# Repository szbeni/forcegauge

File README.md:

# Force Gauge

- ESP32 based Force Gauge - Aiming to help rock climbing specific training (finger excercises)
- Real time plotting via wifi Webapp/Android app

# Pictures
## Forcegauge with fingerboard

## First prototypes

# Hardware
## Main parts
 - ESP32-C3 MCU
 - 3 buttons
 - OLED screen 0.96" SSD1306
 - Battery with charger
 - USB UART connection
 - HX711 ADC - Load cell
## Schematic ##

- [Schematic](https://github.com/szbeni/forcegauge/blob/main/hw/forcegauge/forcegauge.pdf)
## PCB 

Pictures of the PCB:

## Interactive BOM

- [Interactive BOM](https://htmlpreview.github.io/?https://github.com/szbeni/forcegauge/blob/main/hw/forcegauge/bom/ibom.html)

# Software

## Firmware
- Arudino IDE - Some lagging issues due to limitations of arduino environment
- Started wokring on firmware with ESP-IDF which supports multitasking
- Added Bluetooth support to come up as a Tindeq Progressor bluetooth device (https://tindeq.com/product/progressor) (CChange Bluetooth and restart device, WIFI wont work when BT is on)
- Added Bluetooth support to come up as a Climbro bluetooth device (https://climbro.com/) (Change Bluetooth settings and restart device, WIFI wont work when BT is on)

## Flutter based app (Tested on Android)
- Available on Google play: https://play.google.com/store/apps/details?id=com.github.szbeni.forcegauge
- Real time plotting
- Built in tabata timer (Based on https://github.com/insin/tabata_timer)
- Record history of traning 

## Webapp
- Simple webapp served from a HTTP server

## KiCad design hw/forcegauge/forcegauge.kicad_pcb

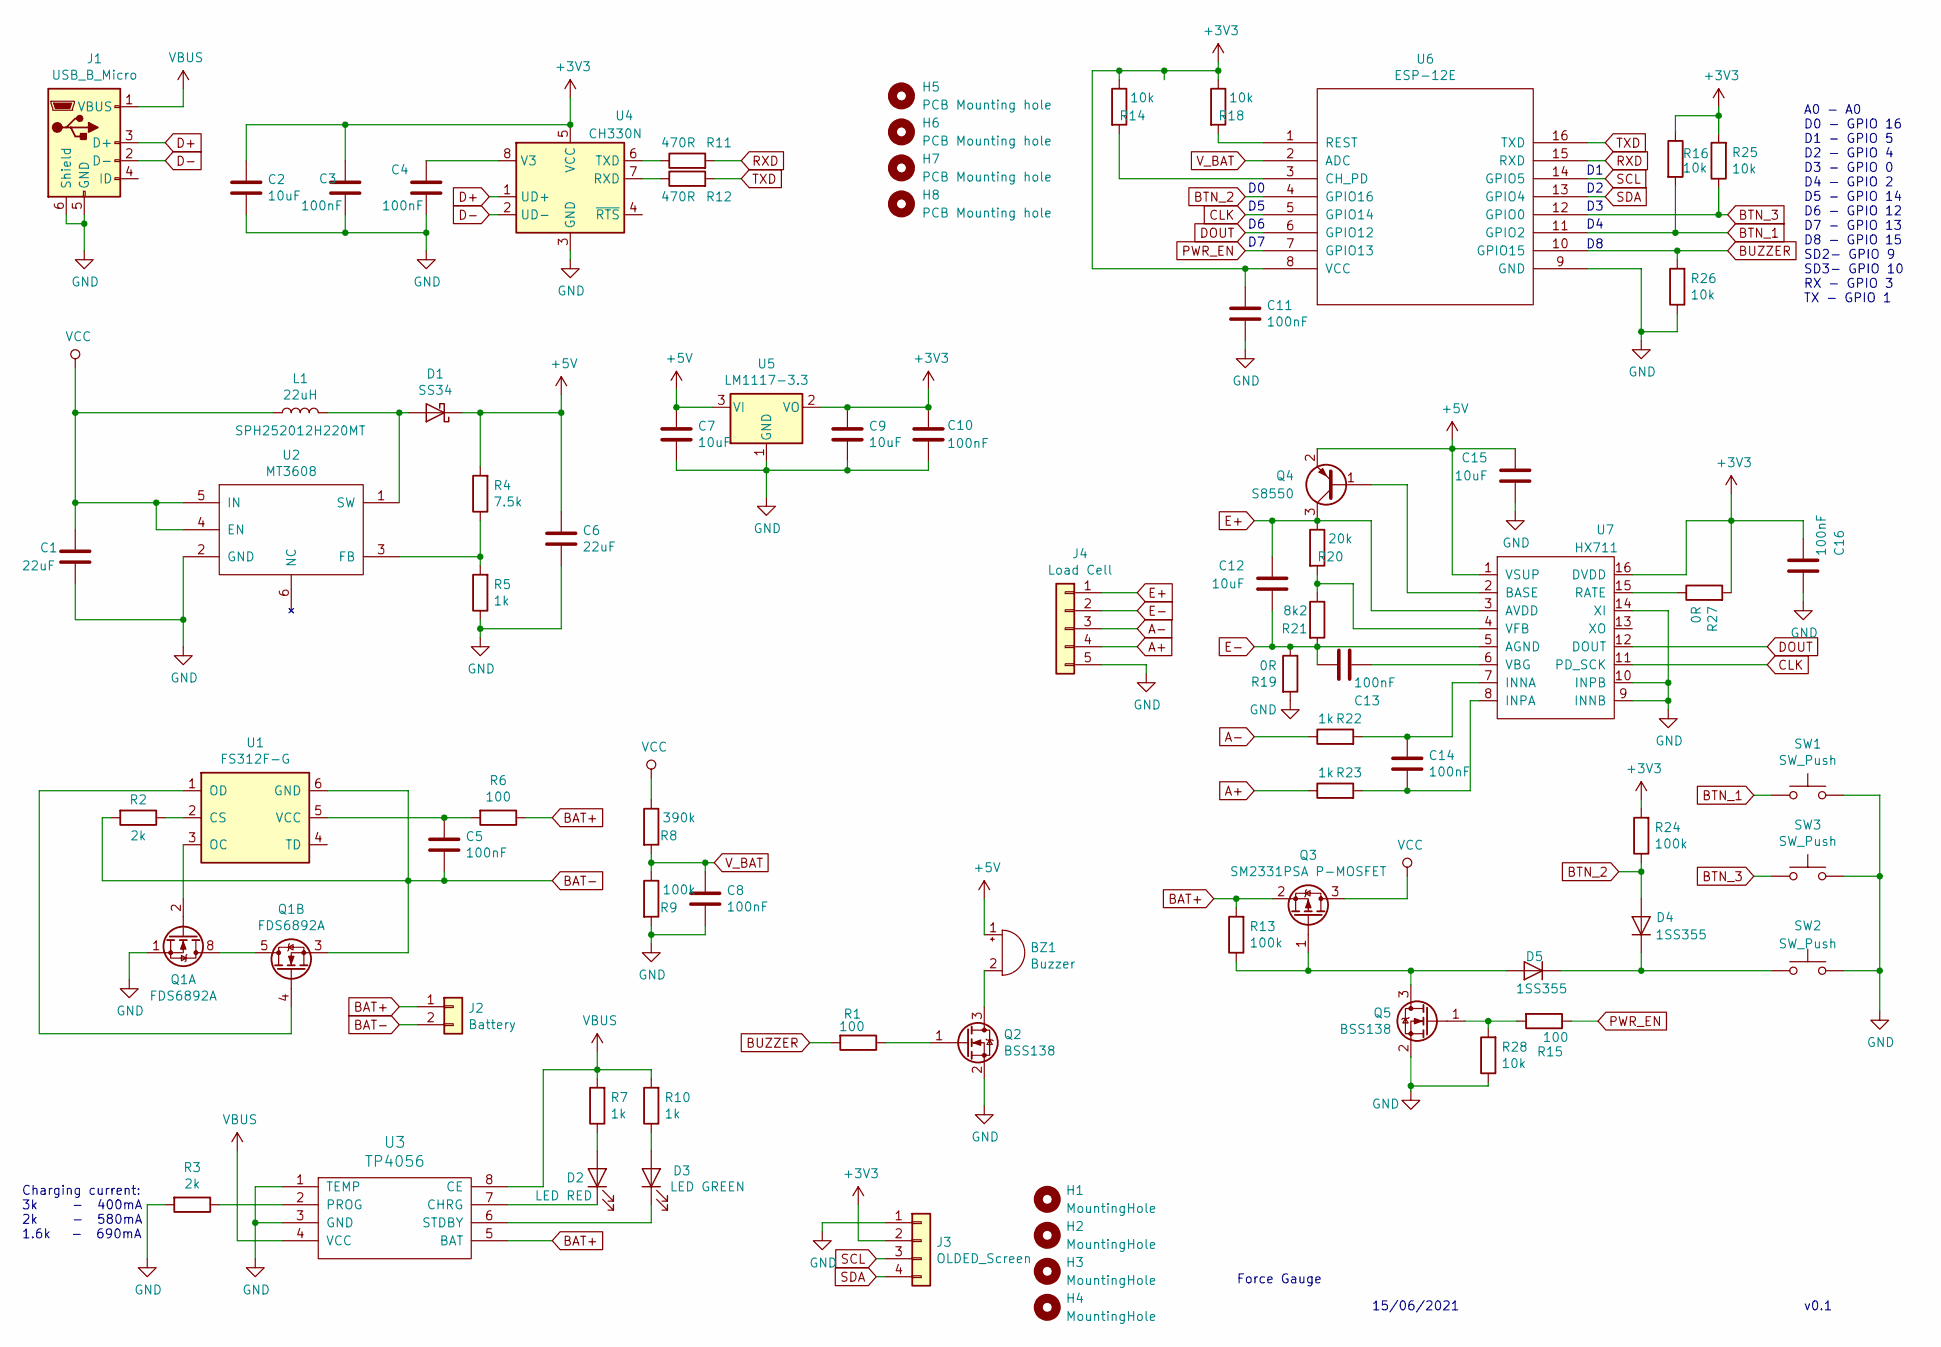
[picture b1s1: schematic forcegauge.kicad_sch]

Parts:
BZ1: Buzzer; Buzzer_12x9.5RM7.6
C1, C6: 22uF; C_1812_4532Metric
C2, C7, C9, C12, C15: 10uF; C_0603_1608Metric
C3, C4, C5, C8, C10, C11, C13, C14, C16: 100nF; C_0603_1608Metric
D1: SS34; D_SMA
D2: LED RED; D_0603_1608Metric
D3: LED GREEN; D_0603_1608Metric
D4, D5: 1SS355; D_SOD-323_HandSoldering
H1, H2, H3, H4: MountingHole; MountingHole_2mm_OLED
H5, H6, H7, H8: PCB Mounting hole; MountingHole_2mm_OLED
J1: USB_B_Micro; USB_Micro-B_Wuerth_629105150521_CircularHoles
J2: Battery; PinHeader_1x02_P2.54mm_Vertical
J3: OLDED_Screen; PinSocket_1x04_P2.54mm_Vertical
J4: Load Cell; PinSocket_1x05_P2.54mm_Vertical
L1: 22uH; L_Wuerth_MAPI-3012
Q1: FDS6892A; SOIC-8_3.9x4.9mm_P1.27mm
Q2, Q5: BSS138; SOT-23
Q3: SM2331PSA P-MOSFET; SOT-23
Q4: S8550; SOT-23
R1, R6, R15: 100; R_0603_1608Metric
R2, R3: 2k; R_0603_1608Metric
R4: 7.5k; R_0603_1608Metric
R5, R7, R10, R22, R23: 1k; R_0603_1608Metric
R8: 390k; R_0603_1608Metric
R9, R13, R24: 100k; R_0603_1608Metric
R11, R12: 470R; R_0603_1608Metric
R14, R16, R18, R25, R26, R28: 10k; R_0603_1608Metric
R19, R27: 0R; R_0603_1608Metric
R20: 20k; R_0603_1608Metric
R21: 8k2; R_0603_1608Metric
SW1, SW2, SW3: SW_Push; SW_PUSH_6mm
U1: FS312F-G; SOT-23-6
U2: MT3608; SOT-23-6
U3: TP4056; SOP8-PP
U4: CH330N; SOIC-8_3.9x4.9mm_P1.27mm
U5: LM1117-3.3; SOT-223
U6: ESP-12E; ESP-12
U7: HX711; SOP-16_4.55x10.3mm_P1.27mm

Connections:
+5V: BZ1.1 (-), C6.1, C7.1, C15.2, D1.1 (K), Q4.2 (E), R4.2, U5.3 (VI), U7.1 (VSUP)
A+: J4.4, R23.1
A-: J4.3, R22.1
BAT+: J2.1, Q3.2 (S), R6.1, R13.2, U3.5 (BAT)
BAT-: C5.2, J2.2, Q1.3 (S2), R2.2, U1.6 (GND)
BTN_1: R16.2, SW1.1, U6.11 (GPIO2)
BTN_2: D4.2 (A), R24.1, U6.4 (GPIO16)
BTN_3: R25.1, SW3.1, U6.12 (GPIO0)
BUZZER: R1.2, R26.2, U6.10 (GPIO15)
CLK: U6.5 (GPIO14), U7.11 (PD_SCK)
D+: J1.3 (D+), U4.1 (UD+)
D-: J1.2 (D-), U4.2 (UD-)
DOUT: U6.6 (GPIO12), U7.12 (DOUT)
E+: C12.2, J4.1, Q4.3 (C), R20.1, U7.3 (AVDD)
E-: C12.1, C13.2, J4.2, R19.1, R21.2, U7.5 (AGND)
GND: C1.2, C2.2, C3.2, C4.2, C6.2, C7.2, C8.2, C9.2, C10.2, C11.2, C15.1, C16.2, J1.5 (GND), J1.6 (Shield), J3.1, J4.5, Q1.1 (S1), Q2.2 (S), Q5.2 (S), R3.2, R5.1, R9.2, R19.2, R26.1, R28.1, SW1.2, SW2.2, SW3.2, U2.2 (GND), U3.1 (TEMP), U3.3 (GND), U4.3 (GND), U5.1 (GND), U6.9 (GND), U7.9 (INNB), U7.10 (INPB), U7.14 (XI)
unnamed: BZ1.2 (+), Q2.3 (D)
unnamed: C4.1, U4.8 (V3)
unnamed: C5.1, R6.2, U1.5 (VCC)
unnamed: C13.1, U7.6 (VBG)
unnamed: C14.1, R22.2, U7.7 (INNA)
unnamed: C14.2, R23.2, U7.8 (INPA)
unnamed: D1.2 (A), L1.2, U2.1 (SW)
unnamed: D2.1 (K), U3.7 (CHRG)
unnamed: D2.2 (A), R7.1
unnamed: D3.1 (K), U3.6 (STDBY)
unnamed: D3.2 (A), R10.1
unnamed: D4.1 (K), D5.1 (K), SW2.1
unnamed: D5.2 (A), Q3.1 (G), Q5.3 (D), R13.1
unnamed: Q1.2 (G1), U1.3 (OC)
unnamed: Q1.4 (G2), U1.1 (OD)
unnamed: Q1.5 (D2), Q1.6 (D2), Q1.7 (D1), Q1.8 (D1)
unnamed: Q2.1 (G), R1.1
unnamed: Q4.1 (B), U7.2 (BASE)
unnamed: Q5.1 (G), R15.2, R28.2
unnamed: R2.1, U1.2 (CS)
unnamed: R3.1, U3.2 (PROG)
unnamed: R4.1, R5.2, U2.3 (FB)
unnamed: R11.1, U4.6 (TXD)
unnamed: R12.1, U4.7 (RXD)
unnamed: R14.2, U6.3 (CH_PD)
unnamed: R18.2, U6.1 (REST)
unnamed: R20.2, R21.1, U7.4 (VFB)
unnamed: R27.1, U7.15 (RATE)
PWR_EN: R15.1, U6.7 (GPIO13)
RXD: R11.2, U6.15 (RXD)
SCL: J3.3, U6.14 (GPIO5)
SDA: J3.4, U6.13 (GPIO4)
TXD: R12.2, U6.16 (TXD)
VBUS: J1.1 (VBUS), R7.2, R10.2, U3.4 (VCC), U3.8 (CE)
VCC: C1.1, L1.1, Q3.3 (D), R8.1, U2.4 (EN), U2.5 (IN)
V_BAT: C8.1, R8.2, R9.1, U6.2 (ADC)

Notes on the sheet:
v0.1
A0 - A0 D0 - GPIO 16 D1 - GPIO 5 D2 - GPIO 4 D3 - GPIO 0 D4 - GPIO 2 D5 - GPIO 14 D6 - GPIO 12 D7 - GPIO 13 D8 - GPIO 15 SD2- GPIO 9 SD3- GPIO 10 RX - GPIO 3 TX - GPIO 1
Force Gauge
15/06/2021
Charging current: 3k - 400mA 2k - 580mA 1.6k - 690mA

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
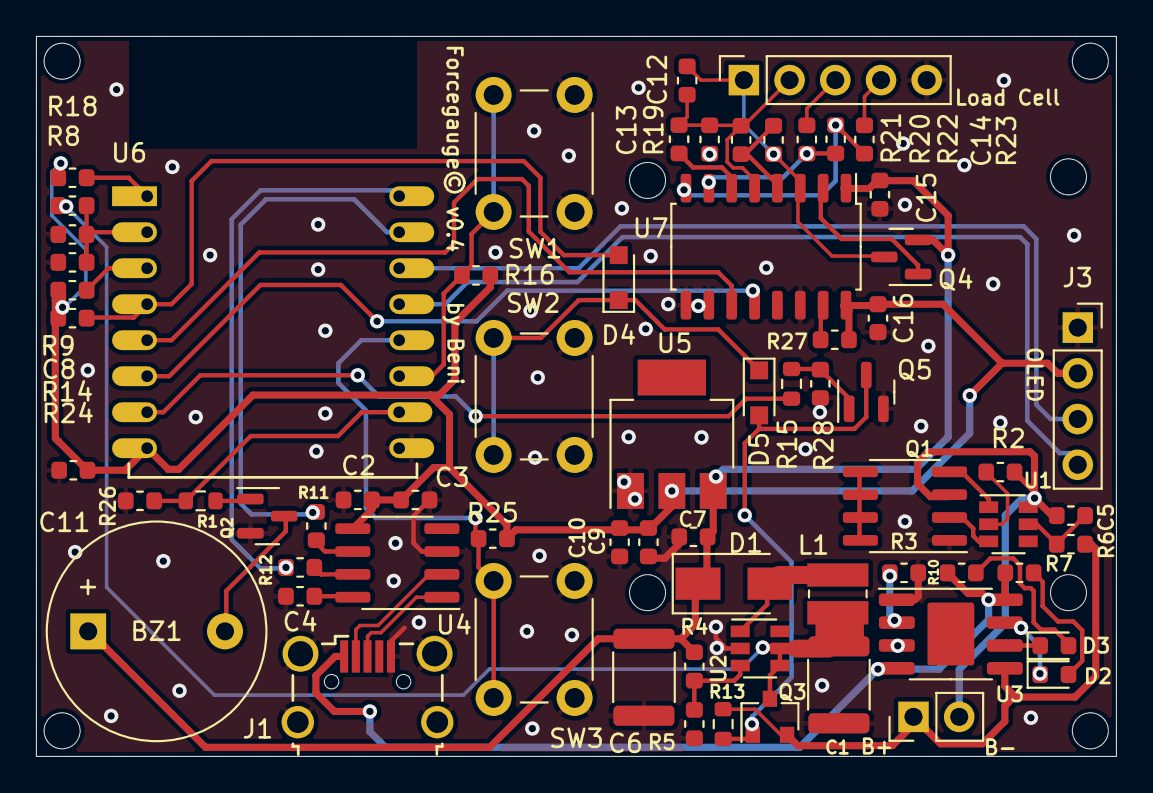
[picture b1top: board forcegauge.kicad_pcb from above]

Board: 2 copper layers, 60.0 x 40.0 mm, 77 parts (0 on the bottom side), 53 nets.

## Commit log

2020-12-26 initial release
2020-12-26 added libs and modified index
2020-12-28 force, index
2020-12-30 ino update
2020-12-31 testdata
2021-01-01 test.html
2021-01-06 added websockets and some other func
2021-01-06 start stop fix
2021-01-13 flutter app started
2021-01-18 graphview update
2021-01-19 added sample device
2021-01-20 graphview improved
2021-02-02 blocify started
2021-02-07 bloc design WIP
2021-02-07 gitignore
2021-02-09 bloc model for settings
2021-02-11 changed graphing
2021-03-28 auto discovery
2021-03-28 added device discovery screen
2021-03-28 network analyzer
2021-03-30 added tabata
2021-03-30 minsdk bump
2021-03-30 warning before break
2021-03-30 warning before break ends fix
2021-03-31 added workout sounds and reportswq
2021-03-31 report screen fix
2021-04-02 screen
2021-04-05 updated pacakges, added custom mp_chart
2021-04-05 addede target force and report graph
2021-04-10 tabata list
2021-04-11 added tabata list and target sounds
2021-04-11 improved graphing
2021-04-11 added history
2021-04-11 graph fixes
2021-04-18 scan device fix, target force fix
2021-05-09 buttons, buzzer, battery voltage
2021-05-15 added button navigation, TODO: clean up the mess:)
2021-05-18 schematic started
2021-05-23 schematic updated
2021-06-15 added schematic
2021-06-15 schematic added
2021-06-15 reorganized folder
2021-06-15 added readme and photos
2021-06-15 readme
2021-06-15 fixed link in readme
2021-06-15 resize image
2021-06-15 resize
2021-06-15 float images
2021-06-26 schematic updated + footprints started
2021-06-26 more footprints
2021-10-09 PCB updates
2021-12-25 added more config
2021-12-28 kicad 6, pcb WIP
2021-12-29 pcb WIP
2022-02-05 pcb routing finished, todo check
2022-02-05 pcb v0.1 sent
2022-02-05 added bom
2022-02-05 render link fix
2022-02-05 render + readme
2022-02-05 readme update
2022-02-08 3d printed box WIP, pcb 3d model
2022-02-17 button dir updated, fixed footprints and changed dual fet
2022-02-19 pcb v0.2 fixed errors
2022-02-20 box updated
2022-02-23 box updateds
2022-02-24 pcb and box updata
2022-02-26 v0.3 pcb
2022-03-10 pcb updated v0.3 working
2022-03-21 pcb v0.4
2022-03-31 started esp idf version
2022-03-31 fix arudino
2022-04-03 work on idf
2022-04-05 esp sdk
2022-04-11 added new photos
2022-04-11 added pdf schematic
2022-04-11 added pdf schematic to readme
2022-04-11 version number updated on schematic
2022-04-11 Fingerboard picture and updated readme
2022-05-02 ditched esp sdk.. change to esp-c3-12f instead which has better library support
2022-05-07 esp32 code started
2022-05-09 esp32 WIP
2022-05-10 esp32-c WIP
2022-05-11 flutter app updated, esp32 nearly working, ranndom crashes..
2022-05-12 dropped asynclibs as they are full of bugs
2022-05-12 captive portal + other fixes
2022-05-13 wifi update
2022-05-13 screen update
2022-05-13 Create fw-esp32.yml
    CI test
2022-05-13 chmod scripts.sh
2022-05-13 CI fix
2022-05-14 bluetooth started, running out of resources..
2022-05-15 settings screen, tabata screen WIP, BLE: TODO
2022-05-16 updated partitions and added mkspiffs and bluetooth enable option, which disables wifi
2022-05-18 tabata cpp started
2022-05-19 workout started
2022-05-21 tabata started on device
2022-05-22 added tabata handler
2022-05-23 added
2022-05-23 tabata added
2022-05-23 Workout buzzing
2022-05-23 added workoutend sound
2022-05-23 workout end buzz tweak
2022-05-24 get tabatas via websocket
2022-05-24 aded option to send tabatas to device
2022-05-26 mnoved out flutter app
2022-06-04 added option to disconnect from wifi
2022-06-10 adc updated, box updated, added flash script
2022-06-16 bugfixes and improvements, dropped bluetooth for now
2022-06-19 broadcast name every 2 secs
2022-06-20 v1.0.2
2022-06-20 flash script
2022-07-02 added udp boradcast message some more HW models
2022-07-03 battery indicator + screen updates
2022-08-21 login page improvements
2022-08-23 more spike filter
2022-08-23 webupdate ota attempt failed added some docs
2023-06-20 excitation voltage resistor values updates
2023-06-20 revert back values as they were right but updated the calculation
2024-06-08 added Tindeq progressor clone via bluetooth
2024-06-08 updated build with nimble
2024-06-08 fixed config save bug
2024-06-08 readme.md
2024-06-09 added climbro bluetooth mode
2024-06-09 readme updated
2024-06-10 added smar
2024-06-10 screen fix for smartboard
2024-06-10 build script update to use cache
2024-07-06 added auto power off
